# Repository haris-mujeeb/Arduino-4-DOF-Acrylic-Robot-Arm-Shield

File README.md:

# 🤖 Arduino 4 DOF Acrylic Robot Arm Shield

This project features an Arduino shield for a simple **4 Degrees of Freedom (DOF)** Acrylic Robot Arm with a robotic gripper claw. 

---

## 📌 Pinout
Connect the Arduino shield as follows:

| Pin Number | Function          | Description                          |
|------------|-------------------|--------------------------------------|
| D9         | Base Servo        | Rotate the base 🌀                  |
| D10        | Shoulder Servo     | Move the shoulder 💪                 |
| D11        | Elbow Servo       | Bend the elbow 🤚                    |
| D3         | Gripper Servo     | Control the gripper claw ✊          |
| D2         | Servo Power Enable | Activate all servos ⚡               |

## 🚀 How to Run It
Use high-speed serial commands at **250000** baud to control the arm via a serial monitor.

### 📅 Basic Workflow:
1. Connect to the Arduino at **250000** baud.
2. Send **E** to power the servos.
3. Use **P** to position the arm.
4. Send **D** to disable servos when done.

### 📜 Commands:
- **🔋 Enable Servos:**
  - **Command**: E
  - **Action**: Powers on servos, allows movement.

- **✋ Disable Servos:**
  - **Command**: D
  - **Action**: Cuts power, servos go limp.

- **🎯 Go to Position:**
  - **Command**: P `<base>` `<shoulder>` `<elbow>` `<wrist>`
  - **Action**: Sets angles (0-180) for each servo. 
  - **Example**: P 90 45 120 180

- **🏠 Home Arm:**
  - **Command**: H
  - **Action**: Returns to home position (Base: 25°, Shoulder: 0°, Elbow: 60°, Wrist: 180°).

---

## 🖼️ Final Board

---

## 📜 License
This project is licensed under the **GNU General Public License (GPL) v3.0**. 
For details, view the full license [here](https://www.gnu.org/licenses/gpl-3.0.html).

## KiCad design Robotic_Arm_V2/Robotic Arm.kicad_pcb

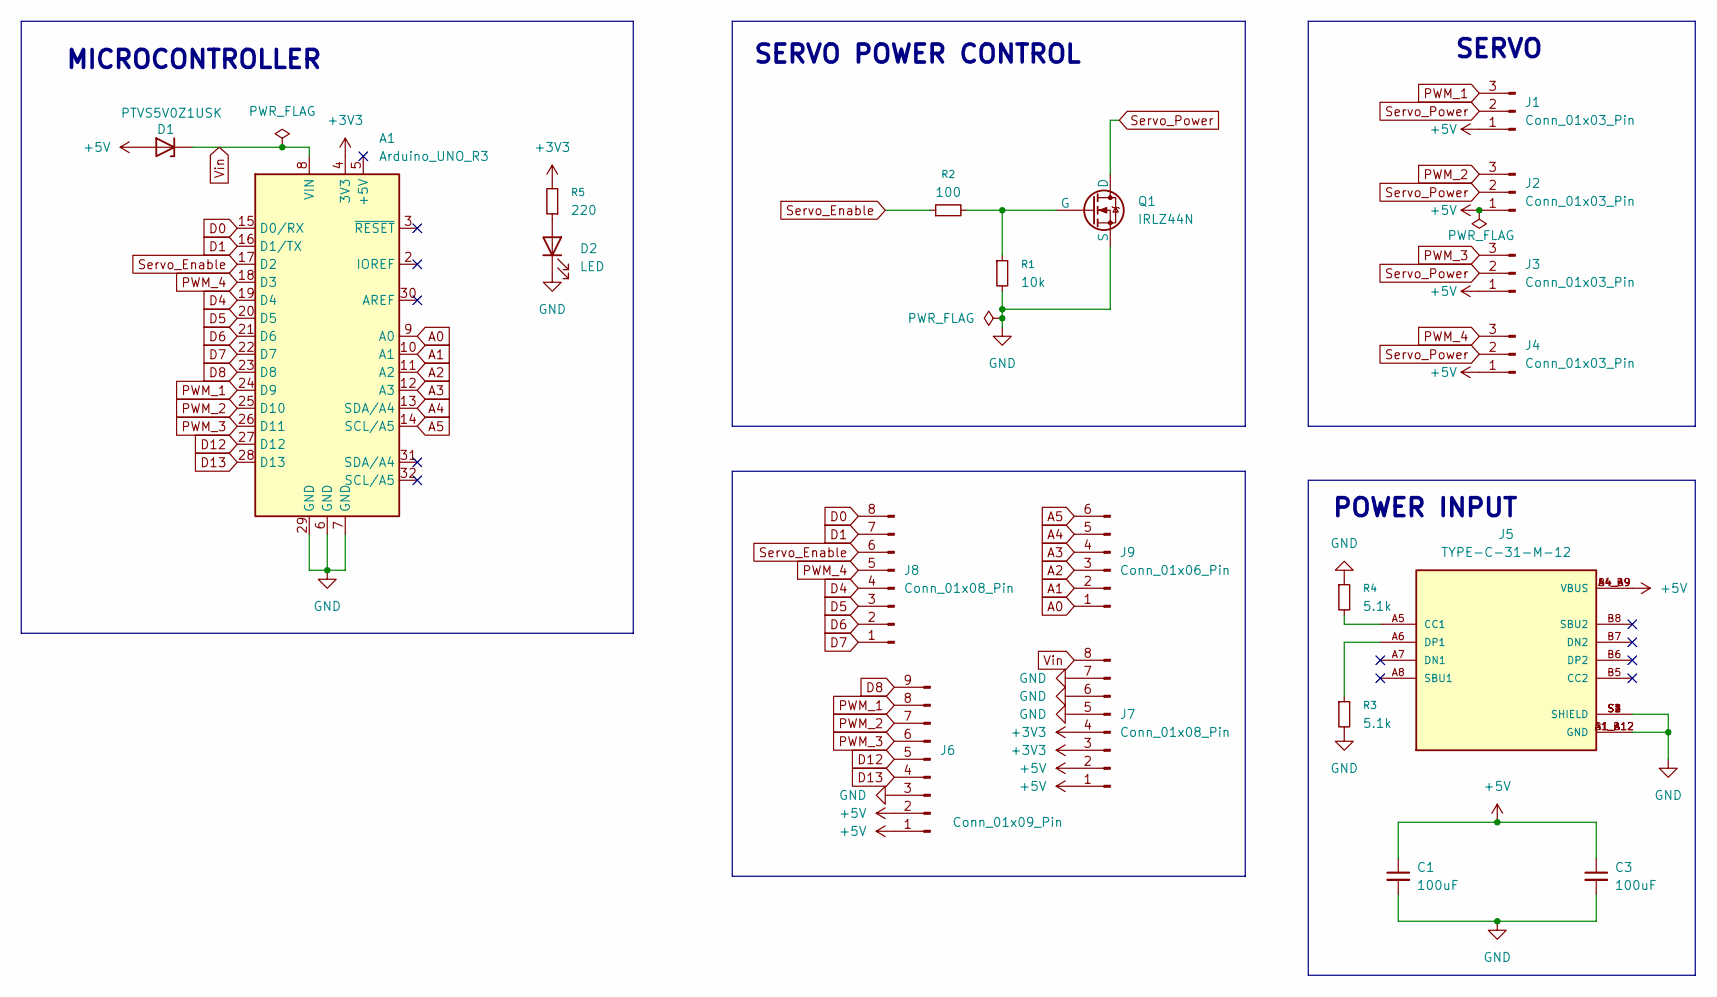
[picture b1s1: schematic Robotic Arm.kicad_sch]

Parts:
A1: Arduino_UNO_R3
C1, C3: 100uF; CP_Radial_D5.0mm_P2.50mm
D1: PTVS5V0Z1USK; D_5W_P10.16mm_Horizontal
D2: LED; LED_D3.0mm
J1, J2, J3, J4: Conn_01x03_Pin; PinHeader_1x03_P2.54mm_Vertical
J5: TYPE-C-31-M-12; HRO_TYPE-C-31-M-12; PARTREV 2020.12.08
J6: Conn_01x09_Pin; PinHeader_1x09_P2.54mm_Vertical
J7, J8: Conn_01x08_Pin; PinHeader_1x08_P2.54mm_Vertical
J9: Conn_01x06_Pin; PinHeader_1x06_P2.54mm_Vertical
Q1: IRLZ44N; TO-220-3_Vertical
R1: 10k; R_Axial_DIN0204_L3.6mm_D1.6mm_P5.08mm_Horizontal
R2: 100; R_Axial_DIN0204_L3.6mm_D1.6mm_P5.08mm_Horizontal
R3, R4: 5.1k; R_Axial_DIN0204_L3.6mm_D1.6mm_P5.08mm_Horizontal
R5: 220; R_Axial_DIN0204_L3.6mm_D1.6mm_P5.08mm_Horizontal

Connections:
+3V3: A1.4 (3V3), J7.3, J7.4, R5.2
+5V: C1.1, C3.1, D1.2 (A), J1.1, J2.1, J3.1, J4.1, J5.A4_B9 (VBUS), J5.B4_A9 (VBUS), J6.1, J6.2, J7.1, J7.2
A0: A1.9 (A0), J9.1
A1: A1.10 (A1), J9.2
A2: A1.11 (A2), J9.3
A3: A1.12 (A3), J9.4
A4: A1.13 (SDA/A4), J9.5
A5: A1.14 (SCL/A5), J9.6
D0: A1.15 (D0/RX), J8.8
D1: A1.16 (D1/TX), J8.7
D4: A1.19 (D4), J8.4
D5: A1.20 (D5), J8.3
D6: A1.21 (D6), J8.2
D7: A1.22 (D7), J8.1
D8: A1.23 (D8), J6.9
D12: A1.27 (D12), J6.5
D13: A1.28 (D13), J6.4
GND: A1.6 (GND), A1.7 (GND), A1.29 (GND), C1.2, C3.2, D2.1 (K), J5.A1_B12 (GND), J5.B1_A12 (GND), J5.S1 (SHIELD), J5.S2 (SHIELD), J5.S3 (SHIELD), J5.S4 (SHIELD), J6.3, J7.5, J7.6, J7.7, Q1.3 (S), R1.2, R3.2, R4.1
unnamed: D2.2 (A), R5.1
unnamed: J5.A5 (CC1), R4.2
unnamed: J5.A6 (DP1), R3.1
unnamed: Q1.2 (G), R1.1, R2.2
PWM_1: A1.24 (D9), J1.3, J6.8
PWM_2: A1.25 (D10), J2.3, J6.7
PWM_3: A1.26 (D11), J3.3, J6.6
PWM_4: A1.18 (D3), J4.3, J8.5
Servo_Enable: A1.17 (D2), J8.6, R2.1
Servo_Power: J1.2, J2.2, J3.2, J4.2, Q1.1 (D)
Vin: A1.8 (VIN), D1.1 (K), J7.8

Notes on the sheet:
POWER INPUT
MICROCONTROLLER
SERVO
SERVO POWER CONTROL

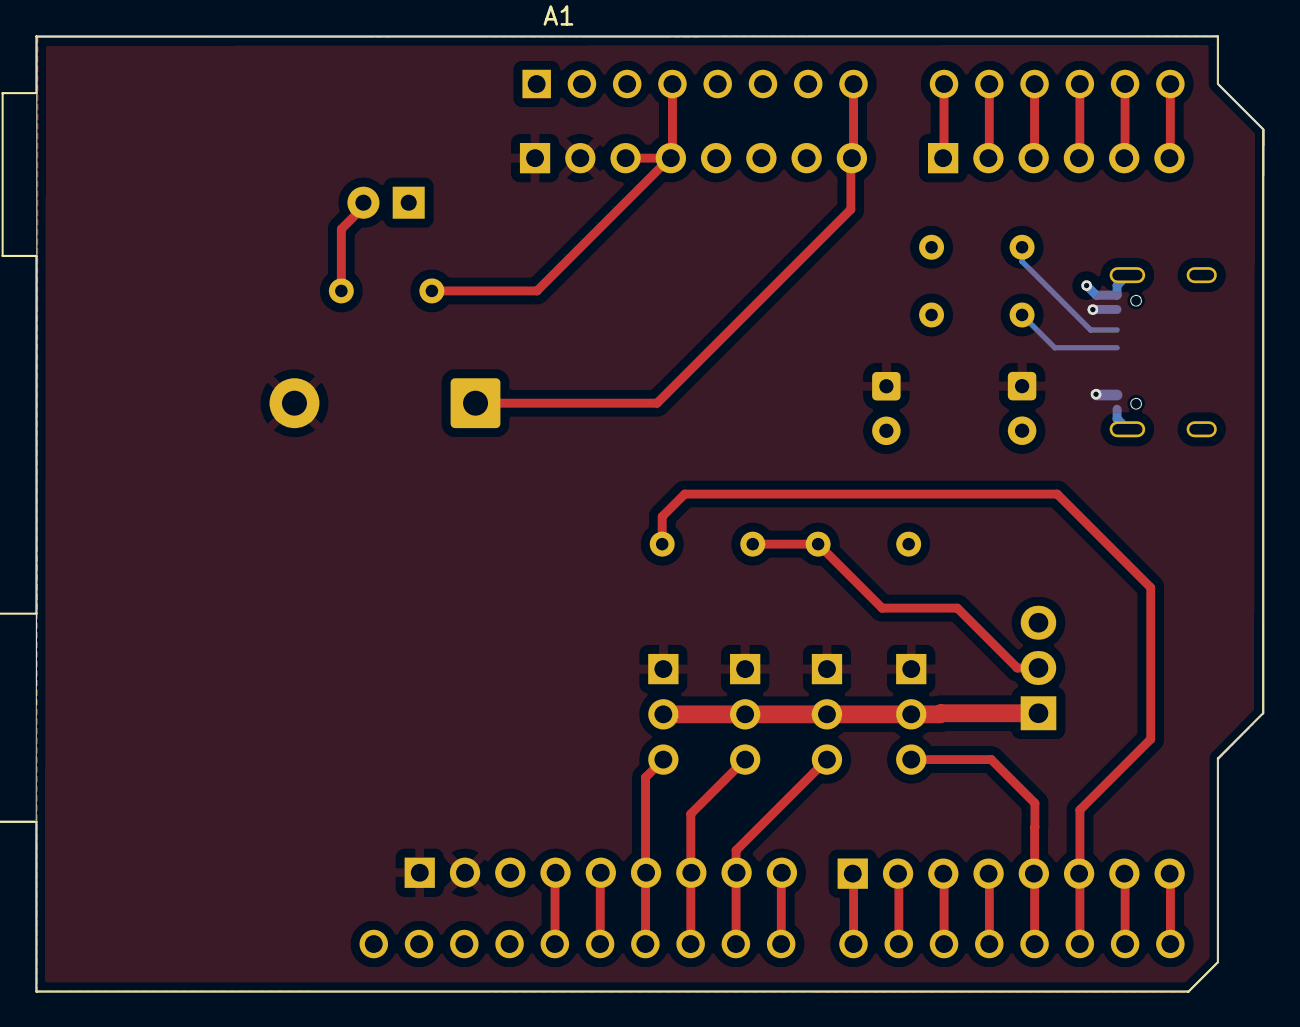
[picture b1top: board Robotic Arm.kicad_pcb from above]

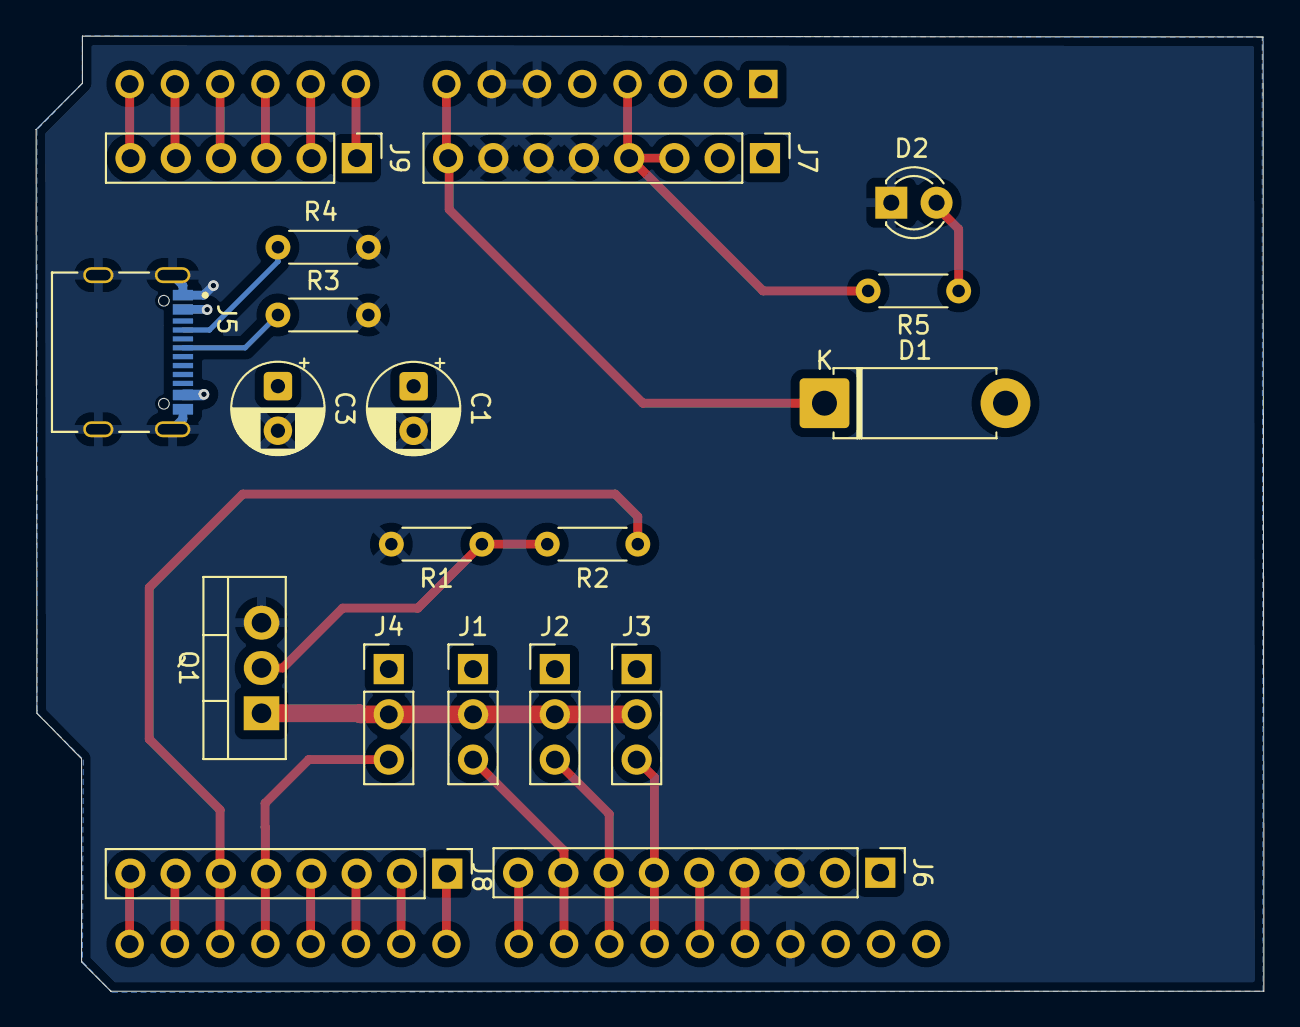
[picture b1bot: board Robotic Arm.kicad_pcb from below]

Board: 2 copper layers, 68.9 x 53.6 mm, 20 parts (19 on the bottom side), 29 nets.

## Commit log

2025-08-24 Add files via upload
    1. 5.1k resistors added for increased current
    2. Digital and Analog interface of Arduino's unused pins
    3. TTL N-Chanel Mosfets added for gate triggering using 5v digital signal from Arduino
2025-08-31 Added Robotic_Arm_V2 design files
2025-08-31 Added Robotic_Arm_V2 as a normal folder (not submodule)
2025-09-16 adjusted folder structure
2025-09-16 renamed
2025-10-20 added 4dof robotic arm library.
2025-10-20 serial iterface added for the 4dof robot
2025-10-20 added Readme
2025-10-20 v1.0
2025-10-21 added basic inverse kinematic control using python
2025-11-02 fixed forward kinematics
2025-11-02 Add dimensions for inverse kinematics calculations
    Added dimensions section with measurements for kinematics.
